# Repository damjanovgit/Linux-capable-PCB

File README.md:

# Linux-capable-PCB
Dizajn štampane pločice i board bring-up za Linux operativni sistem.

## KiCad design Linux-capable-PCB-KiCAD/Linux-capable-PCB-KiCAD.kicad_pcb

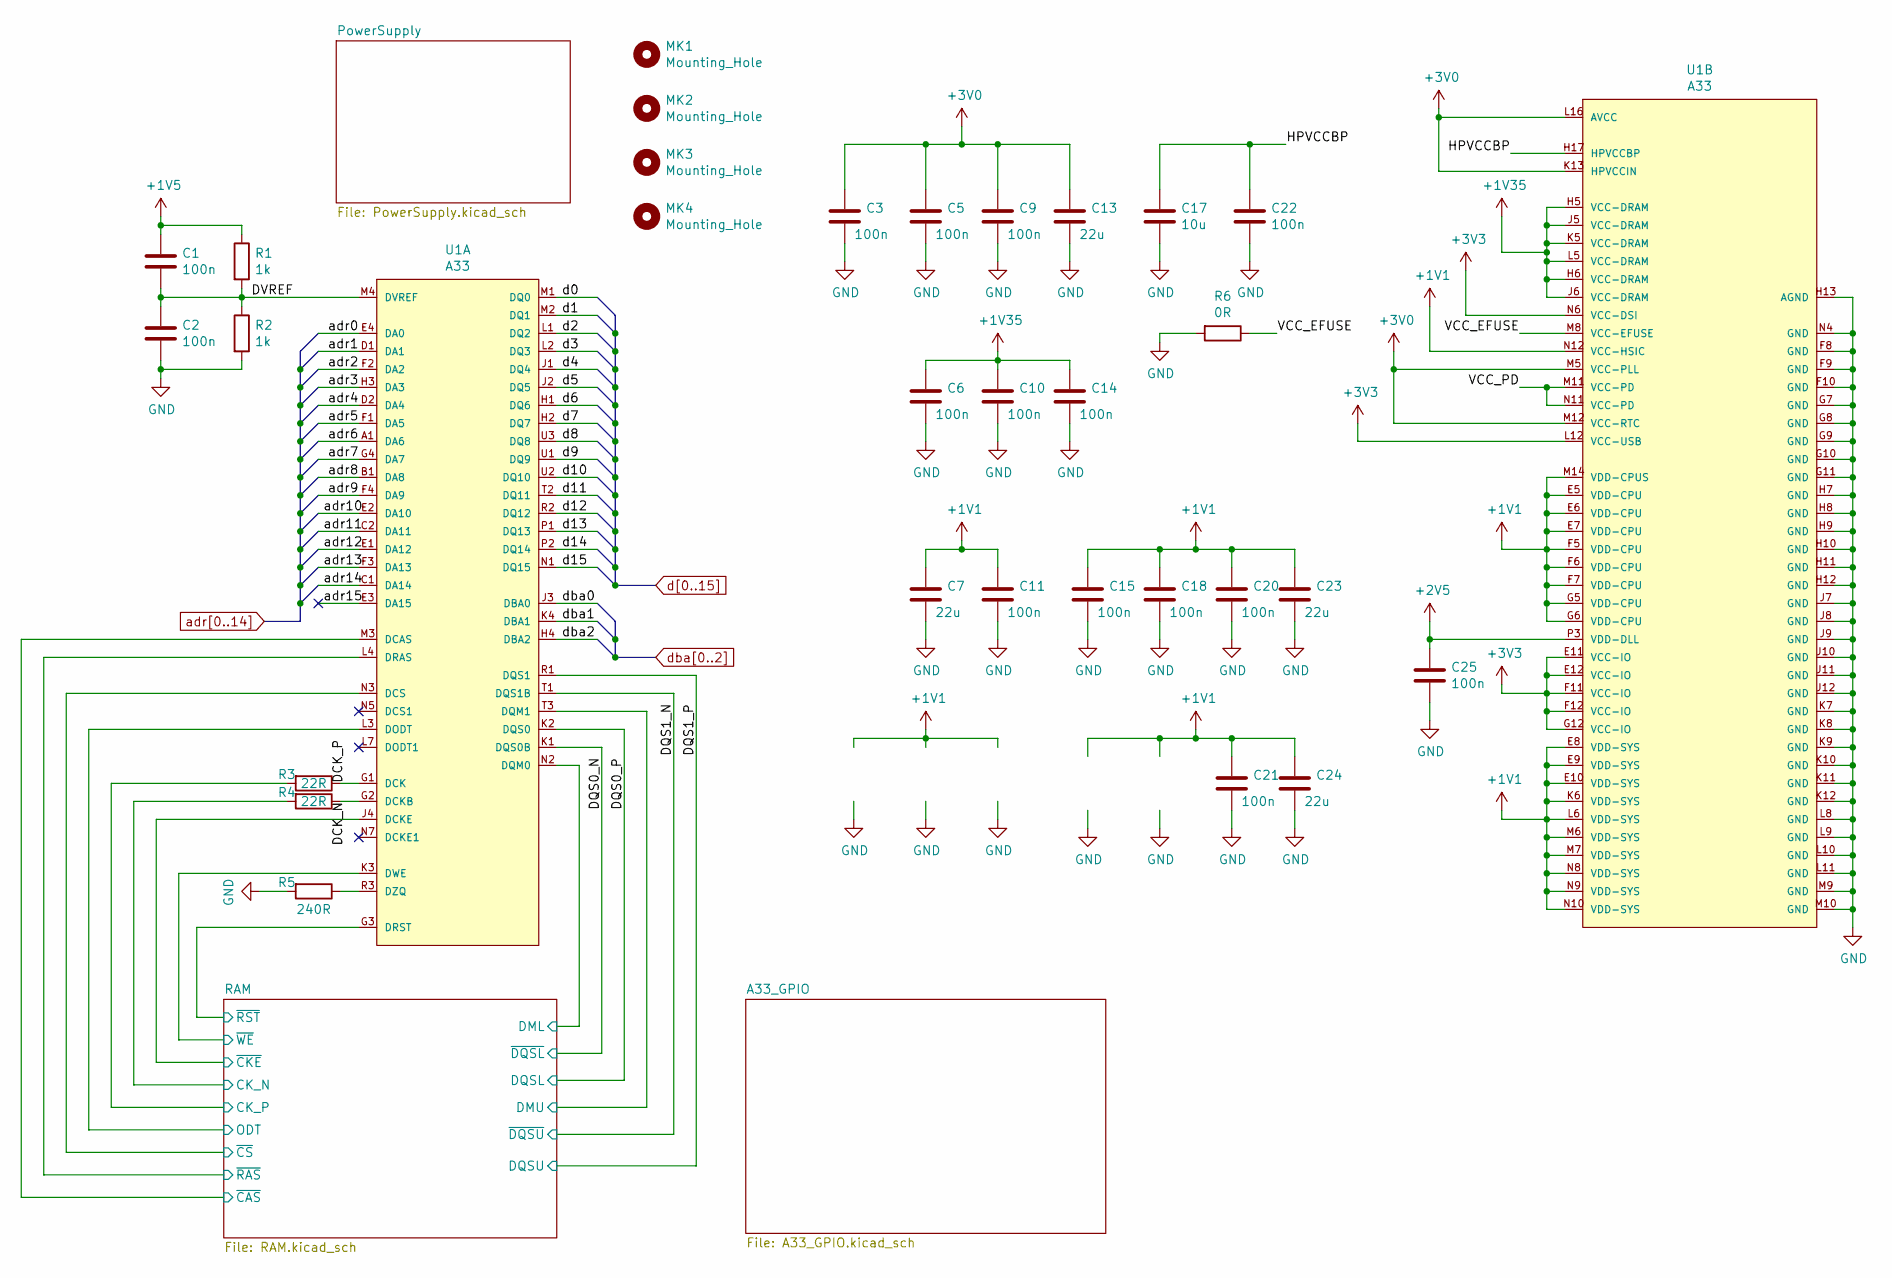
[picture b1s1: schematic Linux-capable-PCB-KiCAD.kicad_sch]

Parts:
C1, C2, C3, C5, C6, C9, C10, C11, C14, C15, C18, C20, C21, C22, C25: 100n; C_0603_1608Metric
C7, C13, C23, C24: 22u; C_0603_1608Metric
C17: 10u; C_0603_1608Metric
MK1, MK2, MK3, MK4: Mounting_Hole; MountingHole_3mm
R1, R2: 1k; R_0603_1608Metric
R3, R4: 22R; R_0603_1608Metric
R5: 240R; R_0603_1608Metric
R6: 0R; R_0603_1608Metric
U1: A33; Allwinner_Technology_Co.,_Ltd.-A33-0

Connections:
+1V1: C7.1, C11.1, C15.1, C18.1, C20.1, C21.1, C23.1, C24.1, U1.E5 (VDD-CPU), U1.E6 (VDD-CPU), U1.E7 (VDD-CPU), U1.E8 (VDD-SYS), U1.E9 (VDD-SYS), U1.E10 (VDD-SYS), U1.F5 (VDD-CPU), U1.F6 (VDD-CPU), U1.F7 (VDD-CPU), U1.G5 (VDD-CPU), U1.G6 (VDD-CPU), U1.K6 (VDD-SYS), U1.L6 (VDD-SYS), U1.M6 (VDD-SYS), U1.M7 (VDD-SYS), U1.M14 (VDD-CPUS), U1.N8 (VDD-SYS), U1.N9 (VDD-SYS), U1.N10 (VDD-SYS), U1.N12 (VCC-HSIC); also elsewhere on the board
+1V5: C1.1, R1.1; also elsewhere on the board
+1V35: C6.1, C10.1, C14.1, U1.H5 (VCC-DRAM), U1.H6 (VCC-DRAM), U1.J5 (VCC-DRAM), U1.J6 (VCC-DRAM), U1.K5 (VCC-DRAM), U1.L5 (VCC-DRAM); also elsewhere on the board
+2V5: C25.1, U1.P3 (VDD-DLL); also elsewhere on the board
+3V0: C3.1, C5.1, C9.1, C13.1, U1.K13 (HPVCCIN), U1.L16 (AVCC), U1.M5 (VCC-PLL), U1.M12 (VCC-RTC); also elsewhere on the board
/DCK_N: R4.1, U1.G2 (DCKB)
/DCK_P: R3.1, U1.G1 (DCK)
/DQS0_N: U1.K1 (DQS0B); also elsewhere on the board
/DQS0_P: U1.K2 (DQS0); also elsewhere on the board
/DQS1_N: U1.T1 (DQS1B); also elsewhere on the board
/DQS1_P: U1.R1 (DQS1); also elsewhere on the board
/DVREF: C1.2, C2.1, R1.2, R2.1, U1.M4 (DVREF)
/HPVCCBP: C17.1, C22.1, U1.H17 (HPVCCBP)
/RAM/CK_N: R4.2; also elsewhere on the board
/RAM/CK_P: R3.2; also elsewhere on the board
/RAM/DML: U1.N2 (DQM0); also elsewhere on the board
/RAM/DMU: U1.T3 (DQM1); also elsewhere on the board
/RAM/ODT: U1.L3 (DODT); also elsewhere on the board
/RAM/~CAS: U1.M3 (DCAS); also elsewhere on the board
/RAM/~CKE: U1.J4 (DCKE); also elsewhere on the board
/RAM/~CS: U1.N3 (DCS); also elsewhere on the board
/RAM/~RAS: U1.L4 (DRAS); also elsewhere on the board
/RAM/~RST: U1.G3 (DRST); also elsewhere on the board
/RAM/~WE: U1.K3 (DWE); also elsewhere on the board
/VCC_EFUSE: R6.1, U1.M8 (VCC-EFUSE)
/VCC_PD: U1.M11 (VCC-PD), U1.N11 (VCC-PD)
/adr15: U1.E3 (DA15)
GND: C2.2, C3.2, C5.2, C6.2, C7.2, C9.2, C10.2, C11.2, C13.2, C14.2, C15.2, C17.2, C18.2, C20.2, C21.2, C22.2, C23.2, C24.2, C25.2, R2.2, R5.2, R6.2, U1.F8 (GND), U1.F9 (GND), U1.F10 (GND), U1.G7 (GND), U1.G8 (GND), U1.G9 (GND), U1.G10 (GND), U1.G11 (GND), U1.H7 (GND), U1.H8 (GND), U1.H9 (GND), U1.H10 (GND), U1.H11 (GND), U1.H12 (GND), U1.H13 (AGND), U1.J7 (GND), U1.J8 (GND), U1.J9 (GND), U1.J10 (GND), U1.J11 (GND), U1.J12 (GND), U1.K7 (GND), U1.K8 (GND), U1.K9 (GND), U1.K10 (GND), U1.K11 (GND), U1.K12 (GND), U1.L8 (GND), U1.L9 (GND), U1.L10 (GND), U1.L11 (GND), U1.M9 (GND), U1.M10 (GND), U1.N4 (GND); also elsewhere on the board
unnamed: R5.1, U1.R3 (DZQ)
adr0: U1.E4 (DA0); also elsewhere on the board
adr1: U1.D1 (DA1); also elsewhere on the board
adr2: U1.F2 (DA2); also elsewhere on the board
adr3: U1.H3 (DA3); also elsewhere on the board
adr4: U1.D2 (DA4); also elsewhere on the board
adr5: U1.F1 (DA5); also elsewhere on the board
adr6: U1.A1 (DA6); also elsewhere on the board
adr7: U1.G4 (DA7); also elsewhere on the board
adr8: U1.B1 (DA8); also elsewhere on the board
adr9: U1.F4 (DA9); also elsewhere on the board
adr10: U1.E2 (DA10); also elsewhere on the board
adr11: U1.C2 (DA11); also elsewhere on the board
adr12: U1.E1 (DA12); also elsewhere on the board
adr13: U1.F3 (DA13); also elsewhere on the board
adr14: U1.C1 (DA14); also elsewhere on the board
d0: U1.M1 (DQ0); also elsewhere on the board
d1: U1.M2 (DQ1); also elsewhere on the board
d2: U1.L1 (DQ2); also elsewhere on the board
d3: U1.L2 (DQ3); also elsewhere on the board
d4: U1.J1 (DQ4); also elsewhere on the board
d5: U1.J2 (DQ5); also elsewhere on the board
d6: U1.H1 (DQ6); also elsewhere on the board
d7: U1.H2 (DQ7); also elsewhere on the board
d8: U1.U3 (DQ8); also elsewhere on the board
d9: U1.U1 (DQ9); also elsewhere on the board
d10: U1.U2 (DQ10); also elsewhere on the board
d11: U1.T2 (DQ11); also elsewhere on the board
d12: U1.R2 (DQ12); also elsewhere on the board
d13: U1.P1 (DQ13); also elsewhere on the board
d14: U1.P2 (DQ14); also elsewhere on the board
d15: U1.N1 (DQ15); also elsewhere on the board
dba0: U1.J3 (DBA0); also elsewhere on the board
dba1: U1.K4 (DBA1); also elsewhere on the board
dba2: U1.H4 (DBA2); also elsewhere on the board

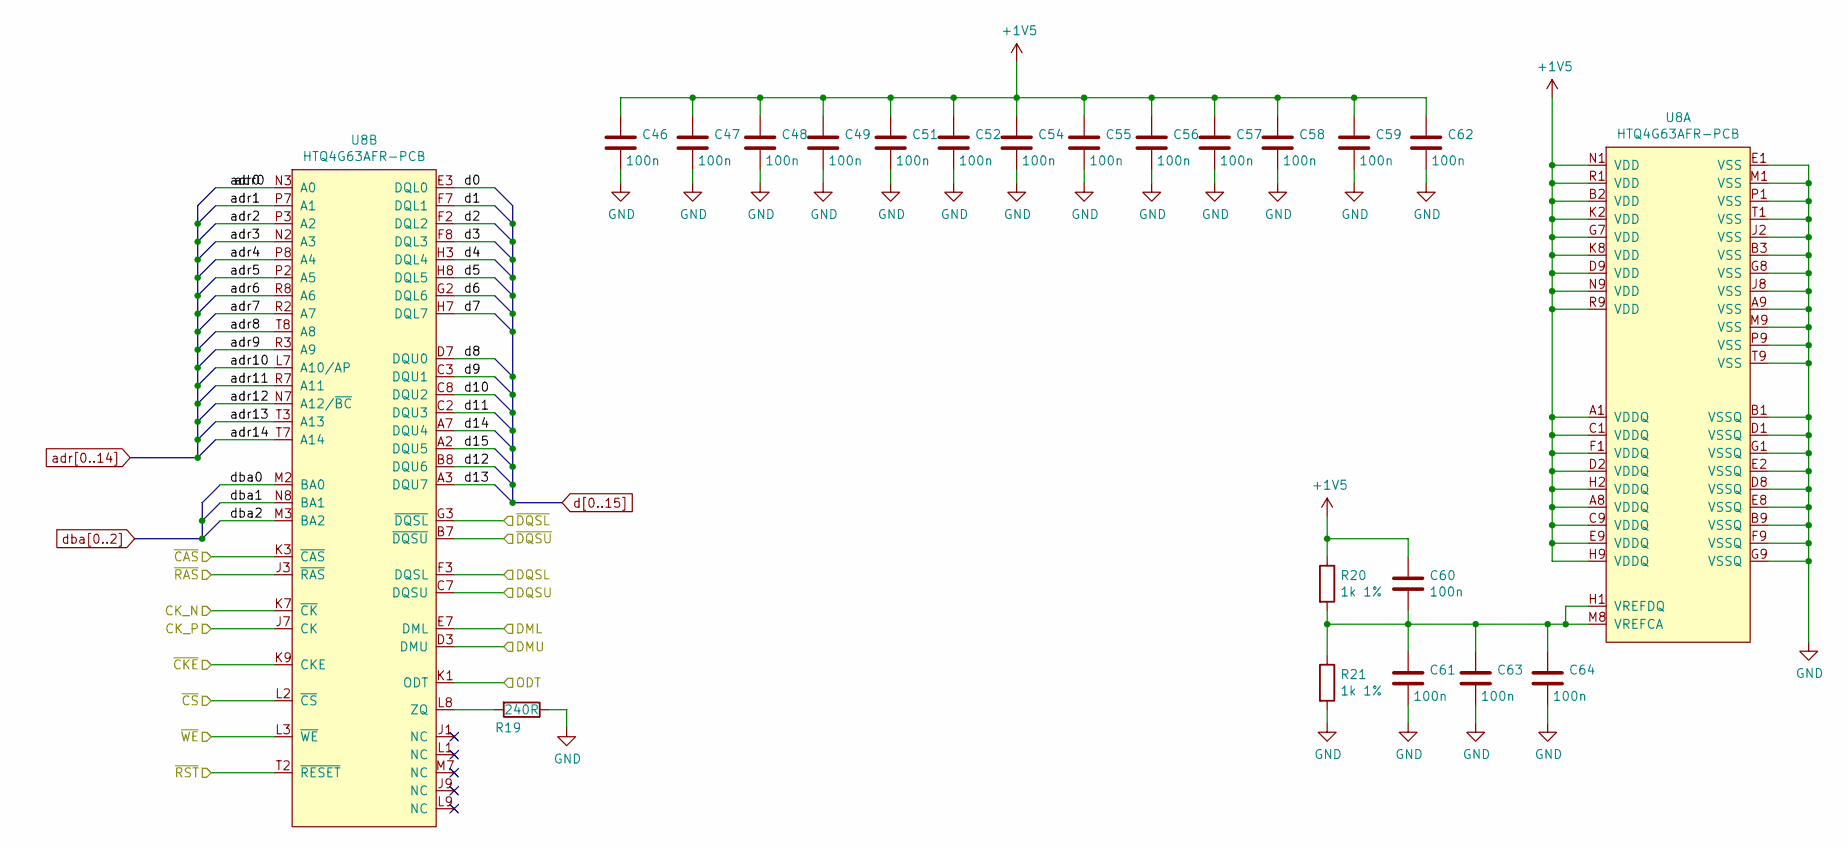
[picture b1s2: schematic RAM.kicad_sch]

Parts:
C46, C47, C48, C49, C51, C52, C54, C55, C56, C57, C58, C59, C60, C61, C62, C63, C64: 100n; C_0603_1608Metric
R19: 240R; R_0603_1608Metric
R20, R21: 1k 1%; R_0603_1608Metric
U8: HTQ4G63AFR-PCB; BGA-96_9.0x13.0mm_Layout2x3x16_P0.8mm

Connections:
+1V5: C46.1, C47.1, C48.1, C49.1, C51.1, C52.1, C54.1, C55.1, C56.1, C57.1, C58.1, C59.1, C60.1, C62.1, R20.1, U8.A1 (VDDQ), U8.A8 (VDDQ), U8.B2 (VDD), U8.C1 (VDDQ), U8.C9 (VDDQ), U8.D2 (VDDQ), U8.D9 (VDD), U8.E9 (VDDQ), U8.F1 (VDDQ), U8.G7 (VDD), U8.H2 (VDDQ), U8.H9 (VDDQ), U8.K2 (VDD), U8.K8 (VDD), U8.N1 (VDD), U8.N9 (VDD), U8.R1 (VDD), U8.R9 (VDD); also elsewhere on the board
/DQS0_N: U8.G3 (~DQSL); also elsewhere on the board
/DQS0_P: U8.F3 (DQSL); also elsewhere on the board
/DQS1_N: U8.B7 (~DQSU); also elsewhere on the board
/DQS1_P: U8.C7 (DQSU); also elsewhere on the board
/RAM/CK_N: U8.K7 (~CK); also elsewhere on the board
/RAM/CK_P: U8.J7 (CK); also elsewhere on the board
/RAM/DML: U8.E7 (DML); also elsewhere on the board
/RAM/DMU: U8.D3 (DMU); also elsewhere on the board
/RAM/ODT: U8.K1 (ODT); also elsewhere on the board
/RAM/~CAS: U8.K3 (~CAS); also elsewhere on the board
/RAM/~CKE: U8.K9 (CKE); also elsewhere on the board
/RAM/~CS: U8.L2 (~CS); also elsewhere on the board
/RAM/~RAS: U8.J3 (~RAS); also elsewhere on the board
/RAM/~RST: U8.T2 (~RESET); also elsewhere on the board
/RAM/~WE: U8.L3 (~WE); also elsewhere on the board
GND: C46.2, C47.2, C48.2, C49.2, C51.2, C52.2, C54.2, C55.2, C56.2, C57.2, C58.2, C59.2, C61.2, C62.2, C63.2, C64.2, R19.1, R21.2, U8.A9 (VSS), U8.B1 (VSSQ), U8.B3 (VSS), U8.B9 (VSSQ), U8.D1 (VSSQ), U8.D8 (VSSQ), U8.E1 (VSS), U8.E2 (VSSQ), U8.E8 (VSSQ), U8.F9 (VSSQ), U8.G1 (VSSQ), U8.G8 (VSS), U8.G9 (VSSQ), U8.J2 (VSS), U8.J8 (VSS), U8.M1 (VSS), U8.M9 (VSS), U8.P1 (VSS), U8.P9 (VSS), U8.T1 (VSS), U8.T9 (VSS); also elsewhere on the board
unnamed: C60.2, C61.1, C63.1, C64.1, R20.2, R21.1, U8.H1 (VREFDQ), U8.M8 (VREFCA)
unnamed: R19.2, U8.L8 (ZQ)
adr0: U8.N3 (A0); also elsewhere on the board
adr1: U8.P7 (A1); also elsewhere on the board
adr2: U8.P3 (A2); also elsewhere on the board
adr3: U8.N2 (A3); also elsewhere on the board
adr4: U8.P8 (A4); also elsewhere on the board
adr5: U8.P2 (A5); also elsewhere on the board
adr6: U8.R8 (A6); also elsewhere on the board
adr7: U8.R2 (A7); also elsewhere on the board
adr8: U8.T8 (A8); also elsewhere on the board
adr9: U8.R3 (A9); also elsewhere on the board
adr10: U8.L7 (A10/AP); also elsewhere on the board
adr11: U8.R7 (A11); also elsewhere on the board
adr12: U8.N7 (A12/~BC); also elsewhere on the board
adr13: U8.T3 (A13); also elsewhere on the board
adr14: U8.T7 (A14); also elsewhere on the board
d0: U8.E3 (DQL0); also elsewhere on the board
d1: U8.F7 (DQL1); also elsewhere on the board
d2: U8.F2 (DQL2); also elsewhere on the board
d3: U8.F8 (DQL3); also elsewhere on the board
d4: U8.H3 (DQL4); also elsewhere on the board
d5: U8.H8 (DQL5); also elsewhere on the board
d6: U8.G2 (DQL6); also elsewhere on the board
d7: U8.H7 (DQL7); also elsewhere on the board
d8: U8.D7 (DQU0); also elsewhere on the board
d9: U8.C3 (DQU1); also elsewhere on the board
d10: U8.C8 (DQU2); also elsewhere on the board
d11: U8.C2 (DQU3); also elsewhere on the board
d12: U8.B8 (DQU6); also elsewhere on the board
d13: U8.A3 (DQU7); also elsewhere on the board
d14: U8.A7 (DQU4); also elsewhere on the board
d15: U8.A2 (DQU5); also elsewhere on the board
dba0: U8.M2 (BA0); also elsewhere on the board
dba1: U8.N8 (BA1); also elsewhere on the board
dba2: U8.M3 (BA2); also elsewhere on the board

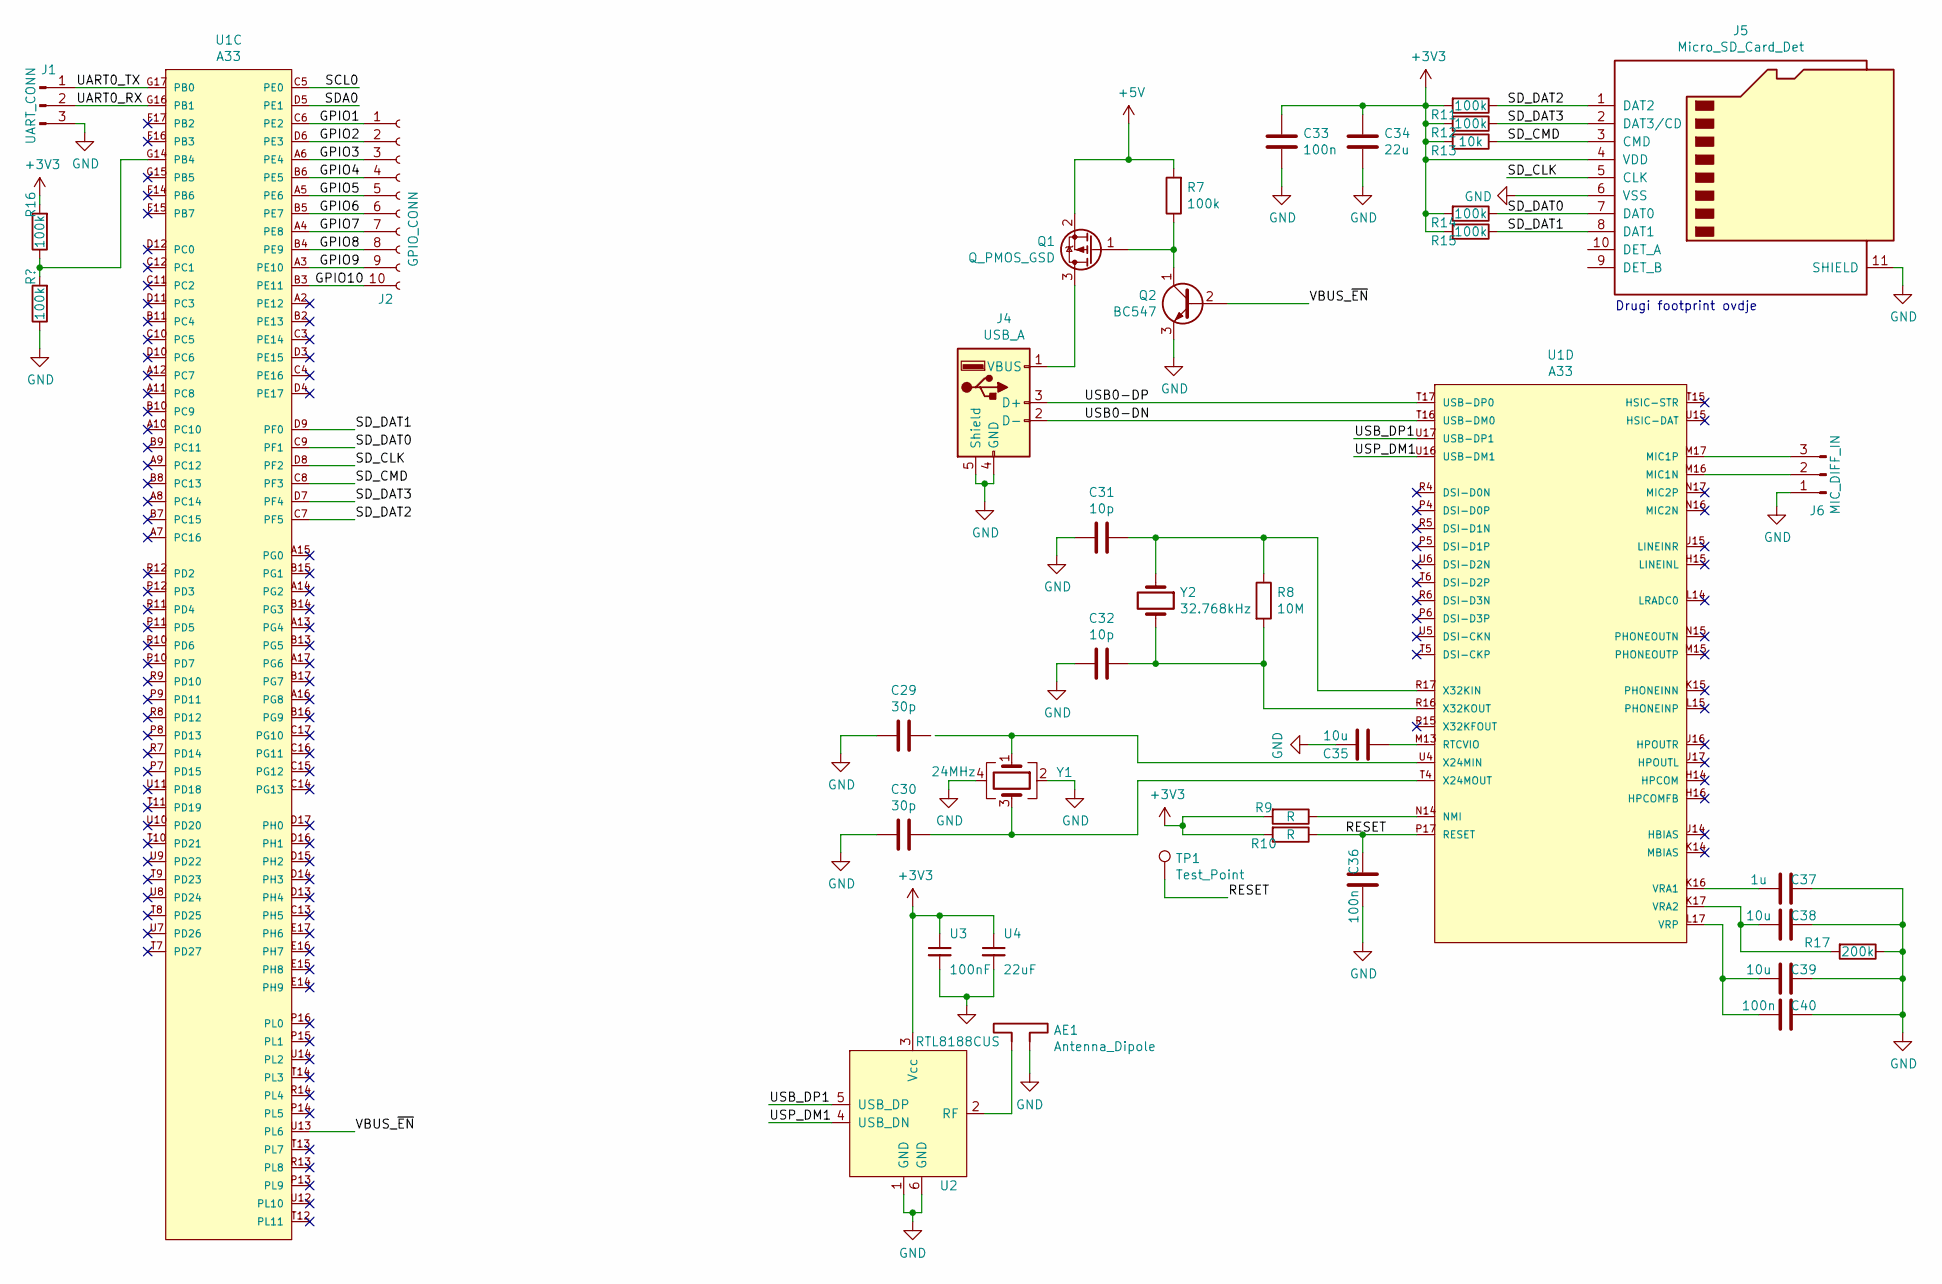
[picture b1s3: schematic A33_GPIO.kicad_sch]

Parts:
AE1: Antenna_Dipole; Small2_4GHz_PCB_Antenna
C29, C30: 30p; C_0603_1608Metric
C31, C32: 10p; C_0603_1608Metric
C33, C36, C40: 100n; C_0603_1608Metric
C34: 22u; C_0603_1608Metric
C35, C38, C39: 10u; C_0603_1608Metric
C37: 1u; C_0603_1608Metric
J1: UART_CONN; PinHeader_1x03_P2.54mm_Vertical
J2: GPIO_CONN; PinHeader_1x10_P2.54mm_Vertical
J4: USB_A; USB_Micro-B_Molex-105017-0001
J5: Micro_SD_Card_Det; microSD_HC_Molex_104031-0811
J6: MIC_DIFF_IN; PinSocket_1x03_P2.54mm_Vertical
Q1: Q_PMOS_GSD
Q2: BC547; TO-92_Molded_Narrow
R7, R11, R12, R14, R15, R16: 100k; R_0603_1608Metric
R8: 10M; R_0603_1608Metric
R9, R10: R; R_0603_1608Metric
R13: 10k; R_0603_1608Metric
R17: 200k; R_0603_1608Metric
TP1: Test_Point; TestPoint_Pad_1.0x1.0mm
U1: A33; Allwinner_Technology_Co.,_Ltd.-A33-0
U2: RTL8188CUS
U3: 100nF; C_0402_1005Metric; MPN CC0402KRX7R7BB104
U4: 22uF; C_0402_1005Metric; MPN GRM155R60J226ME11D
Y1: 24MHz; Crystal_SMD_EuroQuartz_MJ-4Pin_5.0x3.2mm
Y2: 32.768kHz; Crystal_SMD_EuroQuartz_MJ-4Pin_5.0x3.2mm

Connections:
+5V: Q1.2 (S), R7.2; also elsewhere on the board
/A33_GPIO/GPIO1: J2.1, U1.C6 (PE2)
/A33_GPIO/GPIO2: J2.2, U1.D6 (PE3)
/A33_GPIO/GPIO3: J2.3, U1.A6 (PE4)
/A33_GPIO/GPIO4: J2.4, U1.B6 (PE5)
/A33_GPIO/GPIO5: J2.5, U1.A5 (PE6)
/A33_GPIO/GPIO6: J2.6, U1.B5 (PE7)
/A33_GPIO/GPIO7: J2.7, U1.A4 (PE8)
/A33_GPIO/GPIO8: J2.8, U1.B4 (PE9)
/A33_GPIO/GPIO9: J2.9, U1.A3 (PE10)
/A33_GPIO/GPIO10: J2.10, U1.B3 (PE11)
/A33_GPIO/RESET: C36.1, R10.1, TP1.1, U1.P17 (RESET)
/A33_GPIO/SD_CLK: J5.5 (CLK), U1.D8 (PF2); also elsewhere on the board
/A33_GPIO/SD_CMD: J5.3 (CMD), R13.1, U1.C8 (PF3); also elsewhere on the board
/A33_GPIO/SD_DAT0: J5.7 (DAT0), R14.1, U1.C9 (PF1); also elsewhere on the board
/A33_GPIO/SD_DAT1: J5.8 (DAT1), R15.1, U1.D9 (PF0); also elsewhere on the board
/A33_GPIO/SD_DAT2: J5.1 (DAT2), R11.1, U1.C7 (PF5); also elsewhere on the board
/A33_GPIO/SD_DAT3: J5.2 (DAT3/CD), R12.1, U1.D7 (PF4); also elsewhere on the board
/A33_GPIO/UART0_RX: J1.2, U1.G16 (PB1)
/A33_GPIO/UART0_TX: J1.1, U1.G17 (PB0)
/A33_GPIO/USB0-DN: J4.2 (D-), U1.T16 (USB-DM0)
/A33_GPIO/USB0-DP: J4.3 (D+), U1.T17 (USB-DP0)
/A33_GPIO/USB_DP1: U1.U17 (USB-DP1), U2.5 (USB_DP)
/A33_GPIO/USP_DM1: U1.U16 (USB-DM1), U2.4 (USB_DN)
/A33_GPIO/VBUS_~EN: Q2.2 (B), U1.U13 (PL6)
GND: AE1.2, C29.2, C30.2, C31.2, C32.2, C33.2, C34.2, C35.2, C36.2, C37.1, C38.1, C39.1, C40.1, J1.3, J4.4 (GND), J4.5 (Shield), J5.6 (VSS), J5.11 (SHIELD), J6.1, Q2.3 (E), R17.1, U2.1 (GND), U2.6 (GND), U3.2, U4.2, Y1.2, Y1.4; also elsewhere on the board
unnamed: AE1.1, U2.2 (RF)
unnamed: C30.1, U1.T4 (X24MOUT), Y1.3
unnamed: C31.1, R8.1, U1.R17 (X32KIN), Y2.1
unnamed: C32.1, R8.2, U1.R16 (X32KOUT), Y2.2
unnamed: C35.1, U1.M13 (RTCVIO)
unnamed: C37.2, U1.K16 (VRA1)
unnamed: C38.2, R17.2, U1.K17 (VRA2)
unnamed: C39.2, C40.2, U1.L17 (VRP)
unnamed: J4.1 (VBUS), Q1.3 (D)
unnamed: J6.2, U1.M16 (MIC1N)
unnamed: J6.3, U1.M17 (MIC1P)
unnamed: Q1.1 (G), Q2.1 (C), R7.1
unnamed: R9.1, U1.N14 (NMI)
unnamed 84: R16.1, U1.G14 (PB4); also elsewhere on the board
unnamed: U1.U4 (X24MIN), Y1.1

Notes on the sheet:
Drugi footprint ovdje

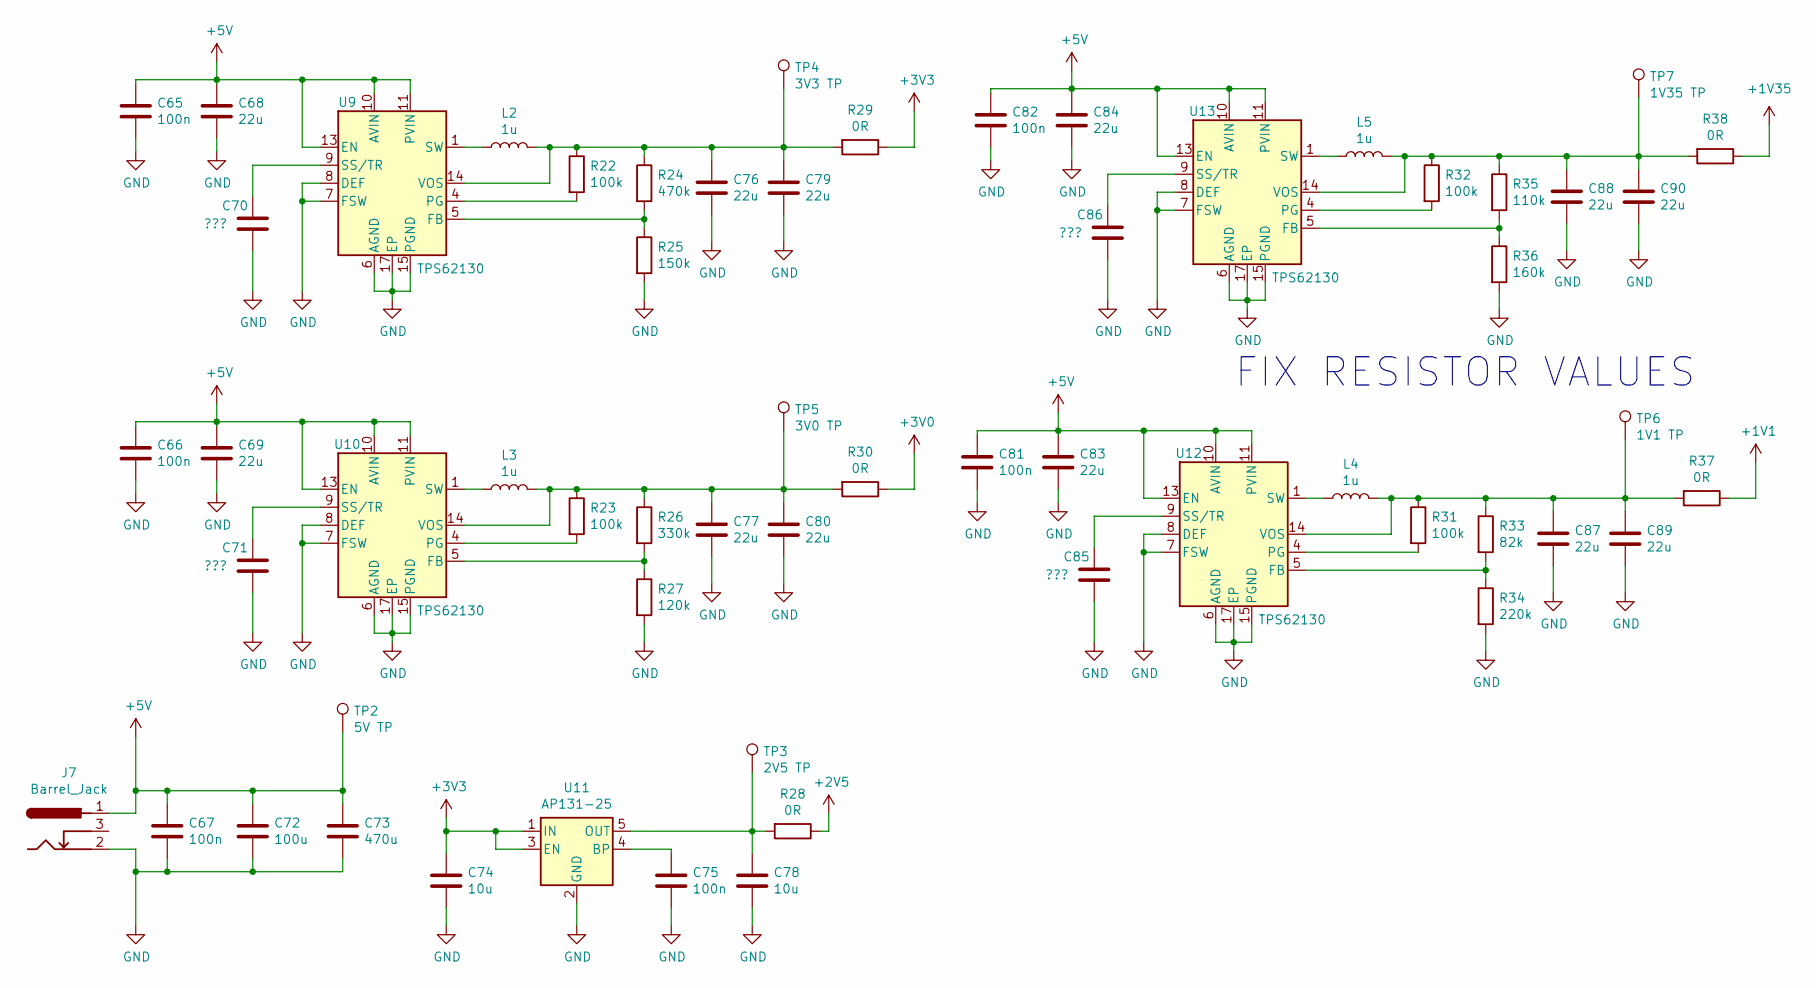
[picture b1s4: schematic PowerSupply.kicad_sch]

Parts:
C65, C66, C67, C75, C81, C82: 100n; C_0603_1608Metric
C68, C69, C76, C77, C79, C80, C83, C84, C87, C88, C89, C90: 22u; C_0603_1608Metric
C70, C71, C85, C86: ???; C_0603_1608Metric
C72: 100u; C_0603_1608Metric
C73: 470u; C_0603_1608Metric
C74, C78: 10u; C_0603_1608Metric
J7: Barrel_Jack; BarrelJack_CUI_PJ-063AH_Horizontal
L2, L3, L4, L5: 1u; L_0603_1608Metric
R22, R23, R31, R32: 100k; R_0603_1608Metric
R24: 470k; R_0603_1608Metric
R25: 150k; R_0603_1608Metric
R26: 330k; R_0603_1608Metric
R27: 120k; R_0603_1608Metric
R28, R29, R30, R37, R38: 0R; R_0603_1608Metric
R33: 82k; R_0603_1608Metric
R34: 220k; R_0603_1608Metric
R35: 110k; R_0603_1608Metric
R36: 160k; R_0603_1608Metric
TP2: 5V TP; TestPoint_Pad_1.0x1.0mm
TP3: 2V5 TP; TestPoint_Pad_1.0x1.0mm
TP4: 3V3 TP; TestPoint_Pad_1.0x1.0mm
TP5: 3V0 TP; TestPoint_Pad_1.0x1.0mm
TP6: 1V1 TP; TestPoint_Pad_1.0x1.0mm
TP7: 1V35 TP; TestPoint_Pad_1.0x1.0mm
U9, U10, U12, U13: TPS62130; QFN-16-1EP_3x3mm_P0.5mm_EP1.7x1.7mm
U11: AP131-25; SOT-23-5

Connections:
+1V1: R37.1; also elsewhere on the board
+1V35: R38.1; also elsewhere on the board
+2V5: R28.1; also elsewhere on the board
+3V0: R30.1; also elsewhere on the board
+5V: C65.1, C66.1, C67.1, C68.1, C69.1, C72.1, C73.1, C81.1, C82.1, C83.1, C84.1, J7.1, TP2.1, U9.10 (AVIN), U9.11 (PVIN), U9.12 (PVIN), U9.13 (EN), U10.10 (AVIN), U10.11 (PVIN), U10.12 (PVIN), U10.13 (EN), U12.10 (AVIN), U12.11 (PVIN), U12.12 (PVIN), U12.13 (EN), U13.10 (AVIN), U13.11 (PVIN), U13.12 (PVIN), U13.13 (EN); also elsewhere on the board
GND: C65.2, C66.2, C67.2, C68.2, C69.2, C70.1, C71.1, C72.2, C73.2, C74.2, C75.2, C76.2, C77.2, C78.2, C79.2, C80.2, C81.2, C82.2, C83.2, C84.2, C85.1, C86.1, C87.2, C88.2, C89.2, C90.2, J7.2, R25.2, R27.2, R34.2, R36.2, U9.6 (AGND), U9.7 (FSW), U9.8 (DEF), U9.15 (PGND), U9.16 (PGND), U9.17 (EP), U10.6 (AGND), U10.7 (FSW), U10.8 (DEF), U10.15 (PGND), U10.16 (PGND), U10.17 (EP), U11.2 (GND), U12.6 (AGND), U12.7 (FSW), U12.8 (DEF), U12.15 (PGND), U12.16 (PGND), U12.17 (EP), U13.6 (AGND), U13.7 (FSW), U13.8 (DEF), U13.15 (PGND), U13.16 (PGND), U13.17 (EP); also elsewhere on the board
unnamed: C70.2, U9.9 (SS/TR)
unnamed: C71.2, U10.9 (SS/TR)
unnamed: C75.1, U11.4 (BP)
unnamed: C76.1, C79.1, L2.2, R22.1, R24.1, R29.2, TP4.1, U9.14 (VOS)
unnamed: C77.1, C80.1, L3.2, R23.1, R26.1, R30.2, TP5.1, U10.14 (VOS)
unnamed: C78.1, R28.2, TP3.1, U11.5 (OUT)
unnamed: C85.2, U12.9 (SS/TR)
unnamed: C86.2, U13.9 (SS/TR)
unnamed: C87.1, C89.1, L4.2, R31.1, R33.1, R37.2, TP6.1, U12.14 (VOS)
unnamed: C88.1, C90.1, L5.2, R32.1, R35.1, R38.2, TP7.1, U13.14 (VOS)
unnamed: L2.1, U9.1 (SW), U9.2 (SW), U9.3 (SW)
unnamed: L3.1, U10.1 (SW), U10.2 (SW), U10.3 (SW)
unnamed: L4.1, U12.1 (SW), U12.2 (SW), U12.3 (SW)
unnamed: L5.1, U13.1 (SW), U13.2 (SW), U13.3 (SW)
unnamed: R22.2, U9.4 (PG)
unnamed: R23.2, U10.4 (PG)
unnamed: R24.2, R25.1, U9.5 (FB)
unnamed: R26.2, R27.1, U10.5 (FB)
unnamed: R31.2, U12.4 (PG)
unnamed: R32.2, U13.4 (PG)
unnamed: R33.2, R34.1, U12.5 (FB)
unnamed: R35.2, R36.1, U13.5 (FB)

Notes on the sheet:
FIX RESISTOR VALUES

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
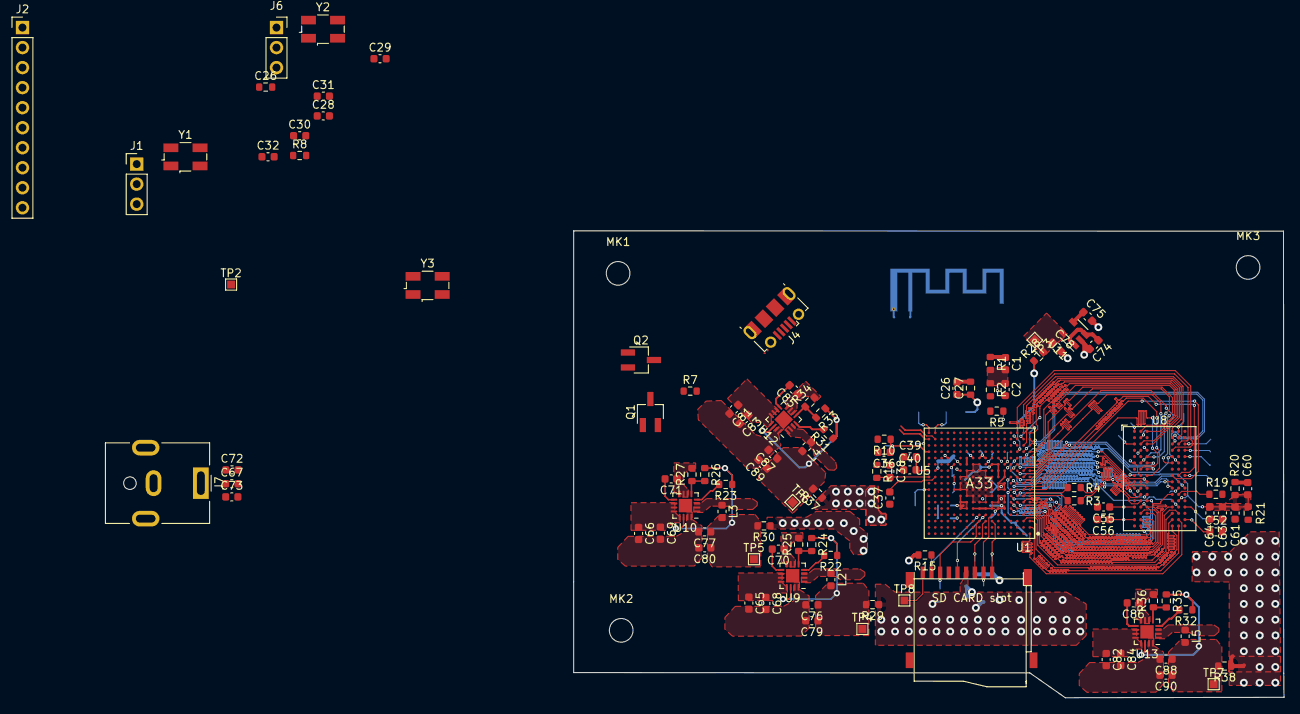
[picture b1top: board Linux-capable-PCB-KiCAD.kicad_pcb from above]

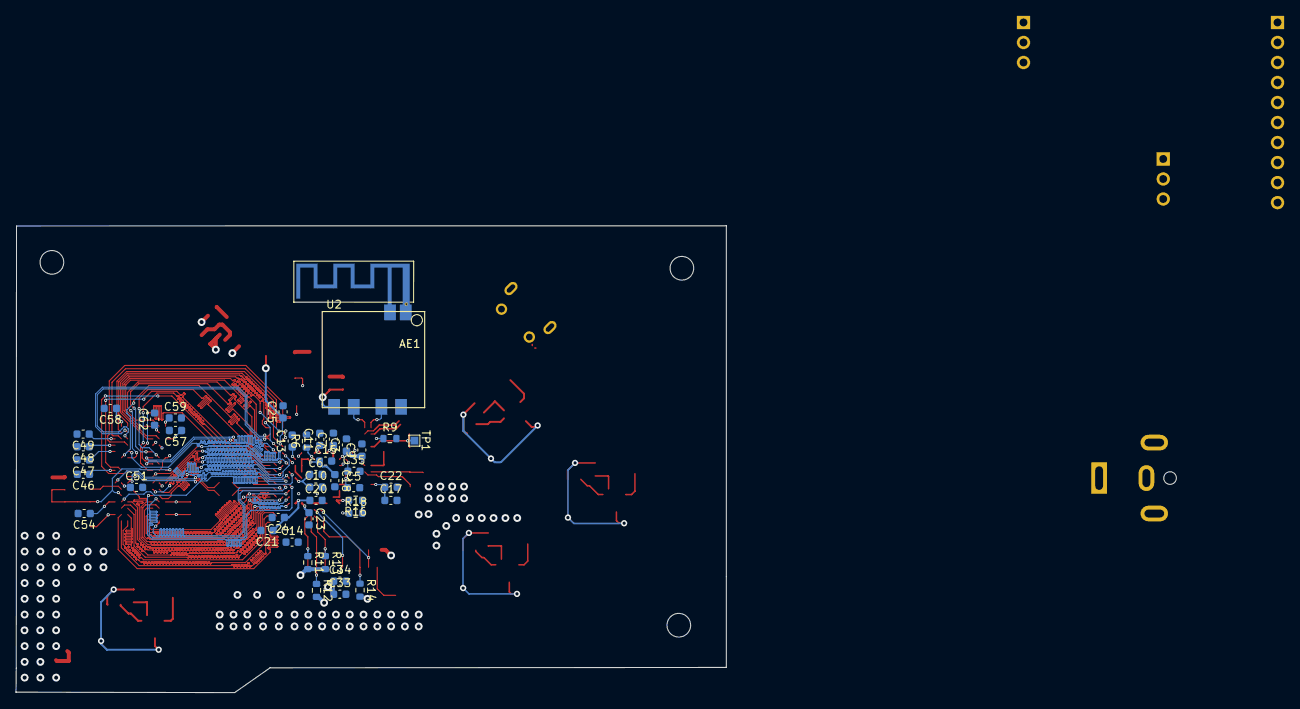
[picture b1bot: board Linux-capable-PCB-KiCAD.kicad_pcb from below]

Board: 4 copper layers, 90.1 x 59.2 mm, 153 parts (42 on the bottom side), 128 nets.

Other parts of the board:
C26, C28: C; C_0603_1608Metric
C26#2: 100nF; R_0603_1608Metric
C27: 22uF; R_0603_1608Metric
R18: 100k; R_0603_1608Metric
TP8: Test_Point; TestPoint_Pad_1.0x1.0mm
U5: SD_card_slot; SD_Card_9_pin_slot
Y3: 26 MHz; Crystal_SMD_EuroQuartz_MJ-4Pin_5.0x3.2mm

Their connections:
/A33_GPIO/SD_CLK: U5.5 (CLK); also elsewhere on the board
/A33_GPIO/SD_CMD: U5.3 (CMD); also elsewhere on the board
/A33_GPIO/SD_DAT0: U5.7 (DAT0); also elsewhere on the board
/A33_GPIO/SD_DAT1: U5.8 (DAT1); also elsewhere on the board
/A33_GPIO/SD_DAT2: U5.1 (DAT2); also elsewhere on the board
/A33_GPIO/SD_DAT3: U5.2 (DAT3); also elsewhere on the board
GND: C26.2, C26#2.2, C27.2, C28.2, R18.1, U5.6 (VSS), U5.10 (VSS), U5.11 (VSS), U5.12 (VSS), U5.13 (VSS), Y3.2, Y3.3; also elsewhere on the board
unnamed 84: R18.2; also elsewhere on the board
unnamed: TP8.1, U5.9 (CARD_DETECT)

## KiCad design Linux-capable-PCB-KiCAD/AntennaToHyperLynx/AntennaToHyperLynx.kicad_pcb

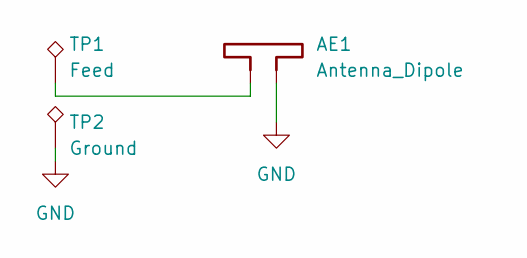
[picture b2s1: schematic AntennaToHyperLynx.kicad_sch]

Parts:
AE1: Antenna_Dipole; Small2_4GHz_PCB_Antenna
TP1: Feed; TestPoint_Pad_D1.0mm
TP2: Ground; TestPoint_Pad_D1.0mm

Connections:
GND: AE1.2, TP2.1
unnamed: AE1.1, TP1.1

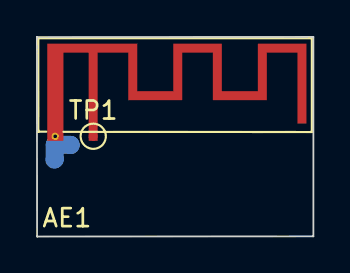
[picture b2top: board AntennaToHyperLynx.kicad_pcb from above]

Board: 2 copper layers, 15.4 x 11.1 mm, 3 parts (1 on the bottom side), 2 nets.

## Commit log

2022-06-08 First
2022-06-13 second push
2022-06-14 neki push
2022-06-14 od kuce
2022-06-20 Added some documents
2022-06-22 RAM cip je spojen
2022-06-23 added ESD protection, g sensor
2022-06-27 Power supply schematics
2022-06-28 Added some footprints
2022-06-28 Assigned footprints to components, antenna and a couple of other footprints need to be assigned
2022-06-28 clearence needs to be resolved
2022-06-29 Some meandering lines added to RAM and processor links
2022-06-30 CPU and RAM
2022-07-01 DDR3 - CPU layout
2022-07-04 CPU and DDR3 connected
2022-07-05 Started designing an antenna
2022-07-06 Added an antenna
2022-07-13 Revert "Od kuce"
    This reverts commit 2bece482254f98a379437a0618b8cb6327aa6629.
2022-09-28 From laptop
2022-10-17 Power supply
2022-10-17 SD card move
2022-11-21 Dodao 3.3V na SD karticu, treba zamjeniti SD konektor, zavrsio napjanje, treba izracunati vrijednosti otpornika i footprint preci za komponente
2022-11-26 message
